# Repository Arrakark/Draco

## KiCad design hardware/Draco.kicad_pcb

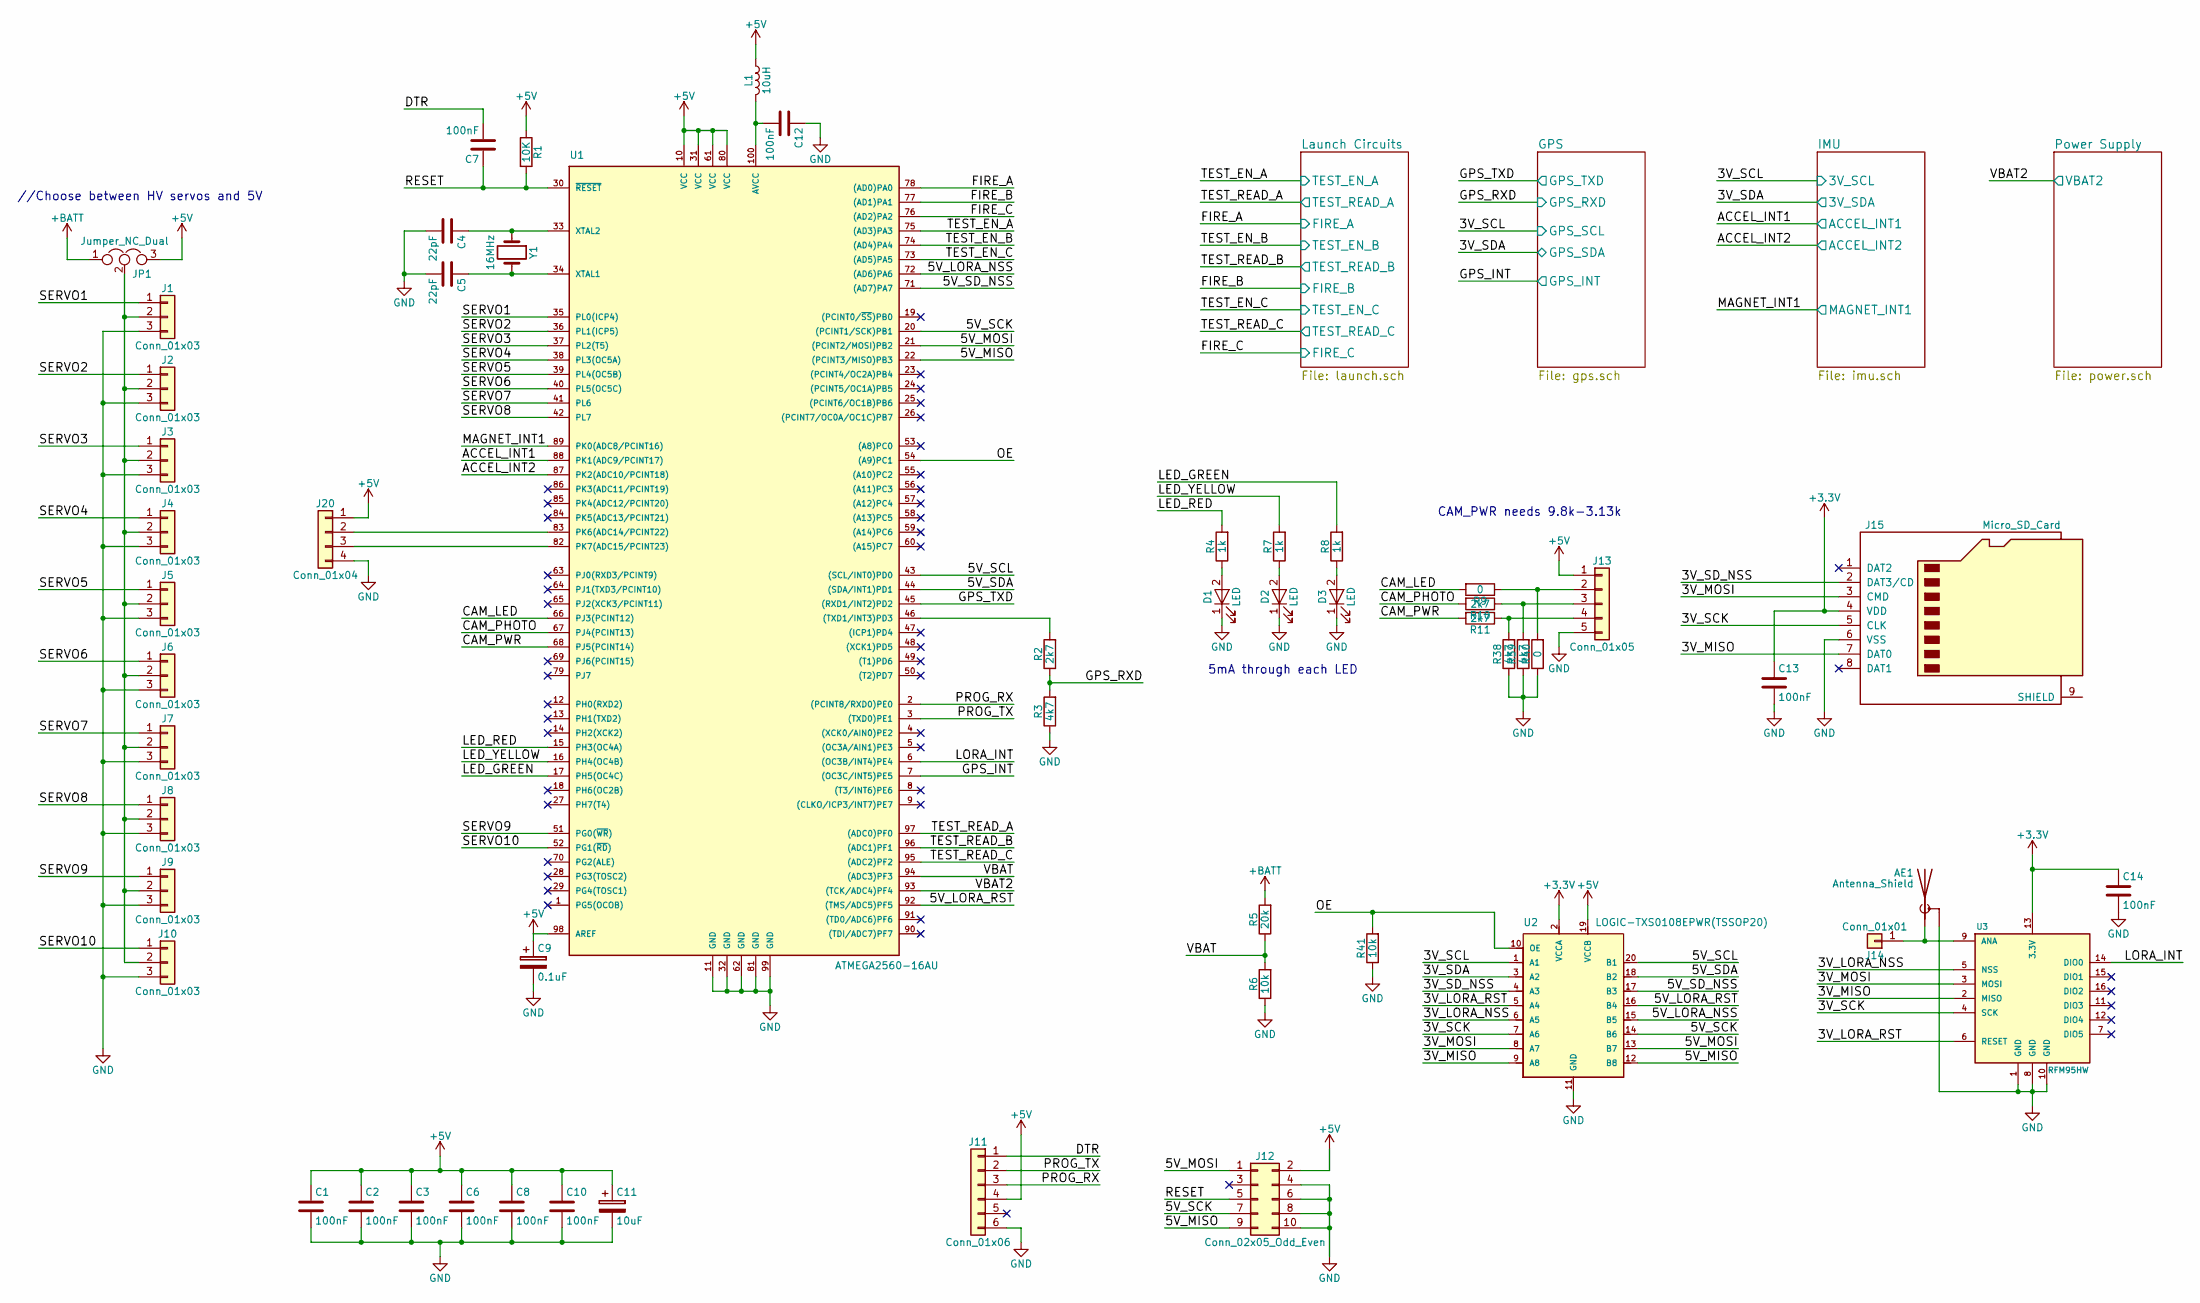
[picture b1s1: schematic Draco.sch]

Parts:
AE1: Antenna_Shield; U.FL-R-SMT
C1, C2, C3, C6, C7, C8, C10, C12, C13, C14: 100nF; C_0805
C4, C5: 22pF; C_0805
C9: 0.1uF; C_0805
C11: 10uF; C_0805
D1, D2, D3: LED; LED_0805
J1, J2, J3, J4, J5, J6, J7, J8, J9, J10: Conn_01x03; Pin_Header_Straight_1x03_Pitch2.54mm
J11: Conn_01x06; Socket_Strip_Straight_1x06_Pitch2.54mm
J12: Conn_02x05_Odd_Even; Pin_Header_Straight_2x05_Pitch2.54mm
J13: Conn_01x05; JST_XH_B05B-XH-A_05x2.50mm_Straight
J14: Conn_01x01; Pin_Header_Straight_1x01_Pitch2.54mm
J15: Micro_SD_Card; microSD_Card_Receptacle_Wuerth_693072010801
J20: Conn_01x04; JST_XH_B04B-XH-A_04x2.50mm_Straight
JP1: Jumper_NC_Dual; Pin_Header_Straight_1x03_Pitch2.54mm
L1: 10uH; L_0805
R1: 10K; R_0805
R2, R10, R11: 2k7; R_0805
R3, R38, R39: 4k7; R_0805
R4, R7, R8: 1k; R_0805
R5: 20k; R_0805
R6, R41: 10k; R_0805
R9, R40: 0; R_0805
U1: ATMEGA2560-16AU; TQFP-100_14x14mm_Pitch0.5mm
U2: LOGIC-TXS0108EPWR(TSSOP20); SSOP-20
U3: RFM95HW; Hopref_RFM9XW_SMD
Y1: 16MHz; Crystal_SMD_HC49-SD

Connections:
+5V: C1.1, C2.1, C3.1, C6.1, C8.1, C9.1, C10.1, C11.1, J11.4, J12.2, J13.1, J20.1, JP1.3, L1.1, R1.1, U1.10 (VCC), U1.31 (VCC), U1.61 (VCC), U1.80 (VCC), U1.98 (AREF), U2.19 (VCCB); also elsewhere on the board
+BATT: JP1.1, R5.2; also elsewhere on the board
/3V_LORA_NSS: U2.6 (A5), U3.5 (NSS)
/3V_LORA_RST: U2.5 (A4), U3.6 (RESET)
/3V_MISO: J15.7 (DAT0), U2.9 (A8), U3.2 (MISO)
/3V_MOSI: J15.3 (CMD), U2.8 (A7), U3.3 (MOSI)
/3V_SCK: J15.5 (CLK), U2.7 (A6), U3.4 (SCK)
/3V_SCL: U2.1 (A1); also elsewhere on the board
/3V_SDA: U2.3 (A2); also elsewhere on the board
/3V_SD_NSS: J15.2 (DAT3/CD), U2.4 (A3)
/5V_LORA_NSS: U1.72 ((AD6)PA6), U2.15 (B5)
/5V_LORA_RST: U1.92 ((TMS/ADC5)PF5), U2.16 (B4)
/5V_MISO: J12.9, U1.22 ((PCINT3/MISO)PB3), U2.12 (B8)
/5V_MOSI: J12.1, U1.21 ((PCINT2/MOSI)PB2), U2.13 (B7)
/5V_SCK: J12.7, U1.20 ((PCINT1/SCK)PB1), U2.14 (B6)
/5V_SCL: U1.43 ((SCL/INT0)PD0), U2.20 (B1)
/5V_SDA: U1.44 ((SDA/INT1)PD1), U2.18 (B2)
/5V_SD_NSS: U1.71 ((AD7)PA7), U2.17 (B3)
/ACCEL_INT1: U1.88 (PK1(ADC9/PCINT17)); also elsewhere on the board
/ACCEL_INT2: U1.87 (PK2(ADC10/PCINT18)); also elsewhere on the board
/CAM_LED: R9.2, U1.66 (PJ3(PCINT12))
/CAM_PHOTO: R10.2, U1.67 (PJ4(PCINT13))
/CAM_PWR: R11.2, U1.68 (PJ5(PCINT14))
/DTR: C7.2, J11.1
/FIRE_A: U1.78 ((AD0)PA0); also elsewhere on the board
/FIRE_B: U1.77 ((AD1)PA1); also elsewhere on the board
/FIRE_C: U1.76 ((AD2)PA2); also elsewhere on the board
/GPS_INT: U1.7 ((OC3C/INT5)PE5); also elsewhere on the board
/GPS_RXD: R2.1, R3.2; also elsewhere on the board
/GPS_TXD: U1.45 ((RXD1/INT2)PD2); also elsewhere on the board
/LED_GREEN: R8.2, U1.17 (PH5(OC4C))
/LED_RED: R4.2, U1.15 (PH3(OC4A))
/LED_YELLOW: R7.2, U1.16 (PH4(OC4B))
/LORA_INT: U1.6 ((OC3B/INT4)PE4), U3.14 (DIO0)
/MAGNET_INT1: U1.89 (PK0(ADC8/PCINT16)); also elsewhere on the board
/OE: R41.2, U1.54 ((A9)PC1), U2.10 (OE)
/PROG_RX: J11.3, U1.2 ((PCINT8/RXD0)PE0)
/PROG_TX: J11.2, U1.3 ((TXD0)PE1)
/RESET: C7.1, J12.5, R1.2, U1.30 (~RESET)
/SERVO1: J1.1, U1.35 (PL0(ICP4))
/SERVO2: J2.1, U1.36 (PL1(ICP5))
/SERVO3: J3.1, U1.37 (PL2(T5))
/SERVO4: J4.1, U1.38 (PL3(OC5A))
/SERVO5: J5.1, U1.39 (PL4(OC5B))
/SERVO6: J6.1, U1.40 (PL5(OC5C))
/SERVO7: J7.1, U1.41 (PL6)
/SERVO8: J8.1, U1.42 (PL7)
/SERVO9: J9.1, U1.51 (PG0(~WR~))
/SERVO10: J10.1, U1.52 (PG1(~RD~))
/TEST_EN_A: U1.75 ((AD3)PA3); also elsewhere on the board
/TEST_EN_B: U1.74 ((AD4)PA4); also elsewhere on the board
/TEST_EN_C: U1.73 ((AD5)PA5); also elsewhere on the board
/TEST_READ_A: U1.97 ((ADC0)PF0); also elsewhere on the board
/TEST_READ_B: U1.96 ((ADC1)PF1); also elsewhere on the board
/TEST_READ_C: U1.95 ((ADC2)PF2); also elsewhere on the board
/VBAT: R5.1, R6.2, U1.94 ((ADC3)PF3)
/VBAT2: U1.93 ((TCK/ADC4)PF4); also elsewhere on the board
GND: AE1.2 (Shield), C1.2, C2.2, C3.2, C4.2, C5.2, C6.2, C8.2, C9.2, C10.2, C11.2, C12.1, C13.2, C14.2, D1.1 (K), D2.1 (K), D3.1 (K), J1.3, J2.3, J3.3, J4.3, J5.3, J6.3, J7.3, J8.3, J9.3, J10.3, J11.6, J12.4, J12.6, J12.8, J12.10, J13.5, J15.6 (VSS), J20.4, R3.1, R6.1, R38.1, R39.1, R40.1, R41.1, U1.11 (GND), U1.32 (GND), U1.62 (GND), U1.81 (GND), U1.99 (GND), U2.11 (GND), U3.1 (GND), U3.8 (GND), U3.10 (GND); also elsewhere on the board
unnamed: AE1.1 (A), J14.1, U3.9 (ANA)
unnamed: C4.1, U1.33 (XTAL2), Y1.1
unnamed: C5.1, U1.34 (XTAL1), Y1.2
unnamed: C12.2, L1.2, U1.100 (AVCC)
unnamed: D1.2 (A), R4.1
unnamed: D2.2 (A), R7.1
unnamed: D3.2 (A), R8.1
unnamed: J1.2, J2.2, J3.2, J4.2, J5.2, J6.2, J7.2, J8.2, J9.2, J10.2, JP1.2
unnamed: J13.2, R9.1, R40.2
unnamed: J13.3, R10.1, R39.2
unnamed: J13.4, R11.1, R38.2
unnamed: J20.2, U1.83 (PK6(ADC14/PCINT22))
unnamed: J20.3, U1.82 (PK7(ADC15/PCINT23))
unnamed: R2.2, U1.46 ((TXD1/INT3)PD3)

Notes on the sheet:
//Choose between HV servos and 5V
5mA through each LED
CAM_PWR needs 9.8k-3.13k

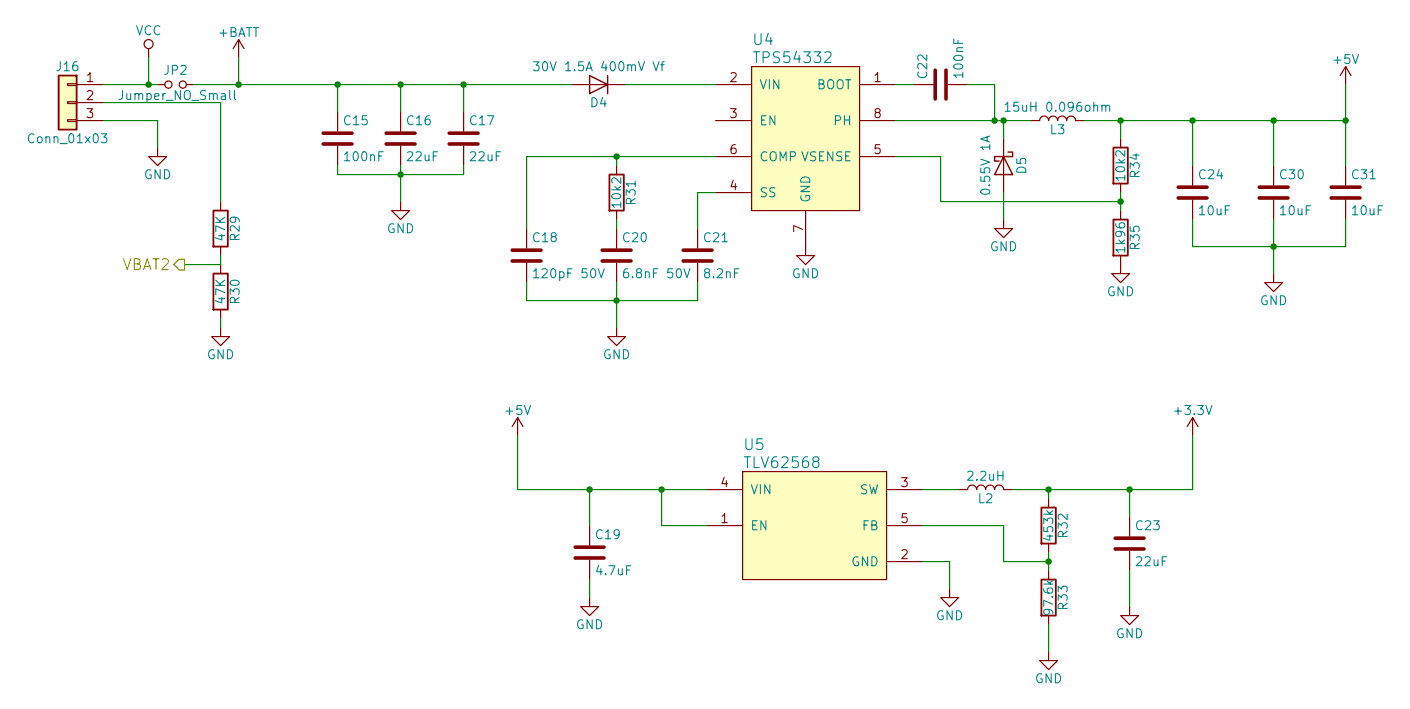
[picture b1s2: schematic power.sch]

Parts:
C15, C22: 100nF; C_0805
C16, C17, C23: 22uF; C_0805
C18: 120pF 50V; C_0805
C19: 4.7uF; C_0805
C20: 6.8nF 50V; C_0805
C21: 8.2nF; C_0805
C24, C30, C31: 10uF; C_0805
D4: 30V 1.5A 400mV Vf; D_SOD-323
D5: 0.55V 1A; D_SOD-123F
J16: Conn_01x03; JST_XH_S03B-XH-A_03x2.50mm_Angled
JP2: Jumper_NO_Small; Pin_Header_Straight_1x02_Pitch2.54mm
L2: 2.2uH; L_Taiyo-Yuden_NR-60xx
L3: 15uH 0.096ohm; L_Taiyo-Yuden_NR-60xx
R29, R30: 47K; R_0805
R31, R34: 10k2; R_0805
R32: 453k; R_0805
R33: 97.6k; R_0805
R35: 1k96; R_0805
U4: TPS54332; SOIC-8-1EP_3.9x4.9mm_Pitch1.27mm
U5: TLV62568; SOT-23-5

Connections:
+5V: C19.1, C24.1, C30.1, C31.1, L3.2, R34.1, U5.1 (EN), U5.4 (VIN); also elsewhere on the board
+BATT: C15.1, C16.1, C17.1, D4.2 (A), JP2.2; also elsewhere on the board
/VBAT2: R29.2, R30.1; also elsewhere on the board
GND: C15.2, C16.2, C17.2, C18.2, C19.2, C20.2, C21.2, C23.2, C24.2, C30.2, C31.2, D5.2 (A), J16.3, R30.2, R33.2, R35.2, U4.7 (GND), U4.9 (GND), U5.2 (GND); also elsewhere on the board
unnamed: C18.1, R31.1, U4.6 (COMP)
unnamed: C20.1, R31.2
unnamed: C21.1, U4.4 (SS)
unnamed: C22.1, U4.1 (BOOT)
unnamed: C22.2, D5.1 (K), L3.1, U4.8 (PH)
unnamed: D4.1 (K), U4.2 (VIN)
unnamed: J16.2, R29.1
unnamed: L2.1, U5.3 (SW)
unnamed: R32.2, R33.1, U5.5 (FB)
unnamed: R34.2, R35.1, U4.5 (VSENSE)
VCC: J16.1, JP2.1; also elsewhere on the board

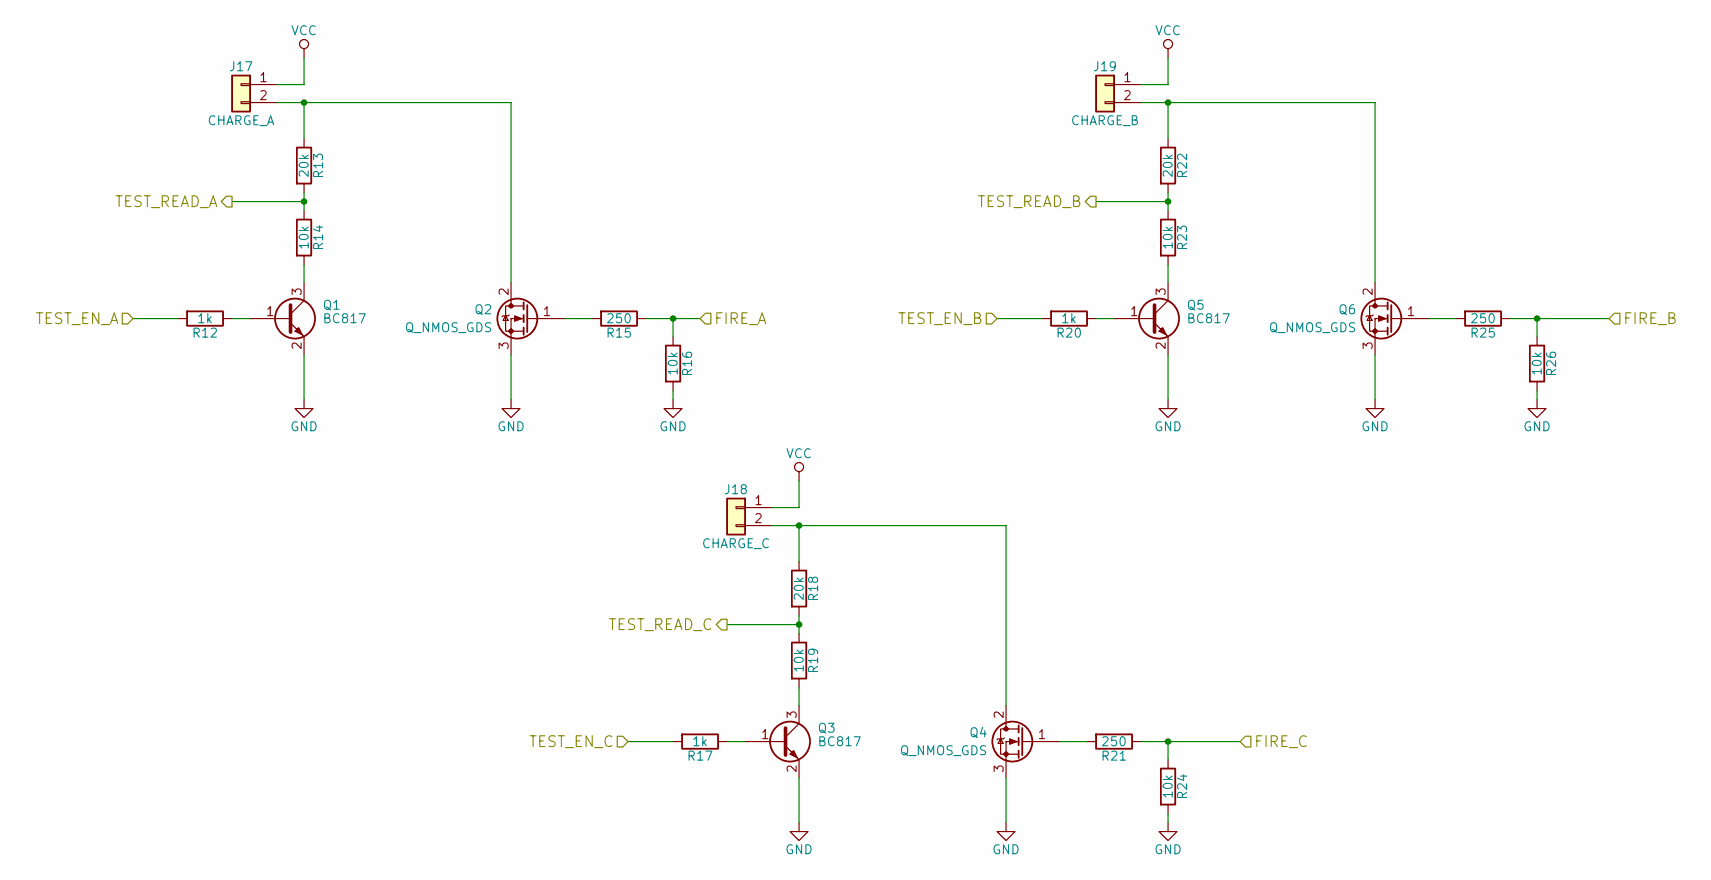
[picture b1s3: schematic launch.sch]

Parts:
J17: CHARGE_A; TerminalBlock_bornier-2_P5.08mm
J18: CHARGE_C; TerminalBlock_bornier-2_P5.08mm
J19: CHARGE_B; TerminalBlock_bornier-2_P5.08mm
Q1, Q3, Q5: BC817; SOT-23
Q2, Q4, Q6: Q_NMOS_GDS; TO-252-2
R12, R17, R20: 1k; R_0805
R13, R18, R22: 20k; R_0805
R14, R16, R19, R23, R24, R26: 10k; R_0805
R15, R21, R25: 250; R_0805

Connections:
/FIRE_A: R15.1, R16.1; also elsewhere on the board
/FIRE_B: R25.1, R26.1; also elsewhere on the board
/FIRE_C: R21.1, R24.1; also elsewhere on the board
/TEST_EN_A: R12.2; also elsewhere on the board
/TEST_EN_B: R20.2; also elsewhere on the board
/TEST_EN_C: R17.2; also elsewhere on the board
/TEST_READ_A: R13.2, R14.1; also elsewhere on the board
/TEST_READ_B: R22.2, R23.1; also elsewhere on the board
/TEST_READ_C: R18.2, R19.1; also elsewhere on the board
GND: Q1.2 (E), Q2.3 (S), Q3.2 (E), Q4.3 (S), Q5.2 (E), Q6.3 (S), R16.2, R24.2, R26.2; also elsewhere on the board
unnamed: J17.2, Q2.2 (D), R13.1
unnamed: J18.2, Q4.2 (D), R18.1
unnamed: J19.2, Q6.2 (D), R22.1
unnamed: Q1.1 (B), R12.1
unnamed: Q1.3 (C), R14.2
unnamed: Q2.1 (G), R15.2
unnamed: Q3.1 (B), R17.1
unnamed: Q3.3 (C), R19.2
unnamed: Q4.1 (G), R21.2
unnamed: Q5.1 (B), R20.1
unnamed: Q5.3 (C), R23.2
unnamed: Q6.1 (G), R25.2
VCC: J17.1, J18.1, J19.1; also elsewhere on the board

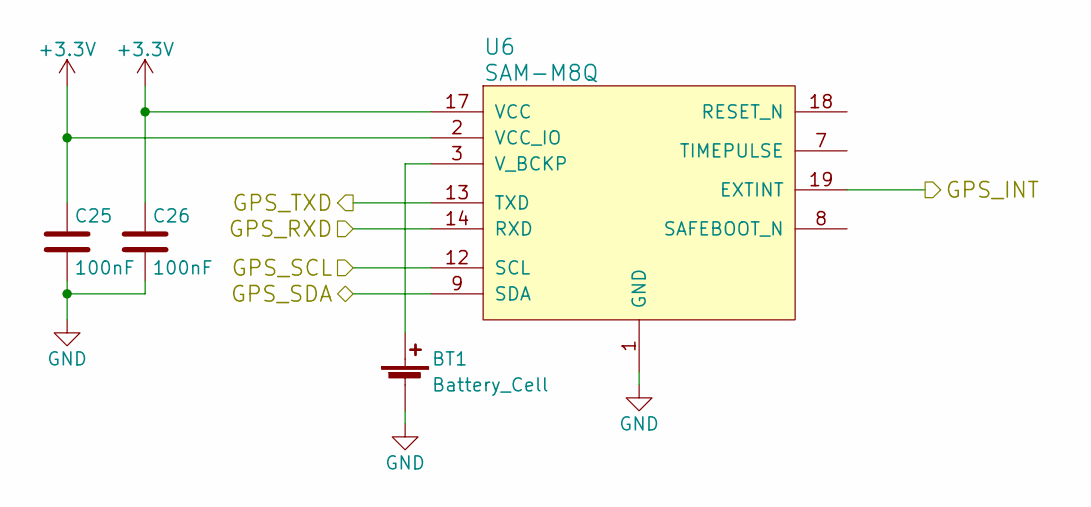
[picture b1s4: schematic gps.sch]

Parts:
BT1: Battery_Cell; Keystone_3000_1x12mm-CoinCell
C25, C26: 100nF; C_0805
U6: SAM-M8Q

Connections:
/3V_SCL: U6.12 (SCL); also elsewhere on the board
/3V_SDA: U6.9 (SDA); also elsewhere on the board
/GPS_INT: U6.19 (EXTINT); also elsewhere on the board
/GPS_RXD: U6.14 (RXD); also elsewhere on the board
/GPS_TXD: U6.13 (TXD); also elsewhere on the board
GND: BT1.2 (-), C25.2, C26.2, U6.1 (GND), U6.4 (GND), U6.5 (GND), U6.6 (GND), U6.10 (GND), U6.11 (GND), U6.15 (GND), U6.16 (GND), U6.20 (GND); also elsewhere on the board
unnamed: BT1.1 (+), U6.3 (V_BCKP)

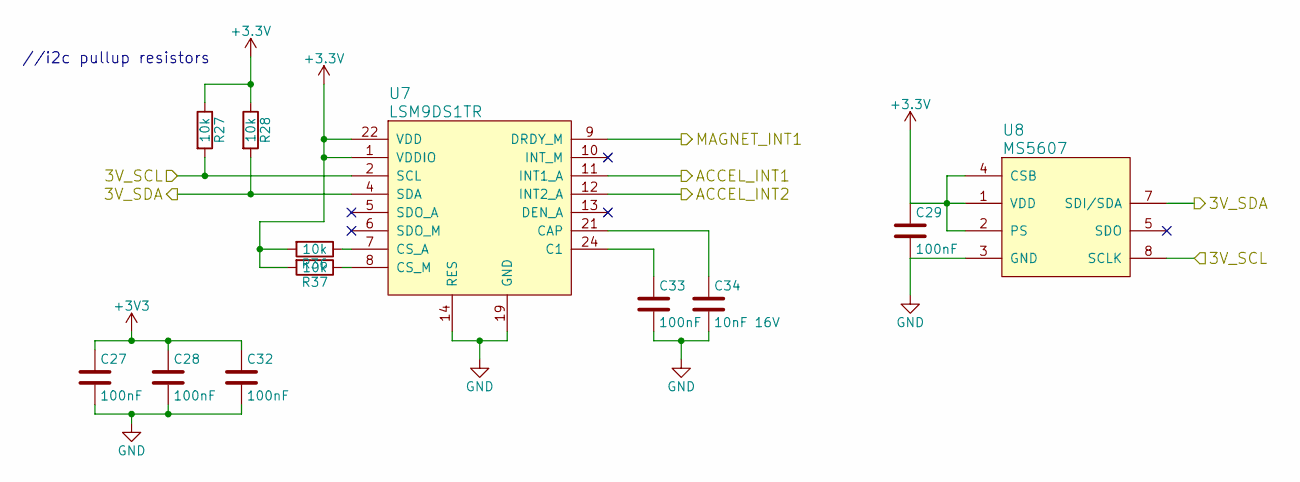
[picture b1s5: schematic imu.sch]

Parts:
C27, C28, C29, C32, C33: 100nF; C_0805
C34: 10nF 16V; C_0805
R27, R28, R36, R37: 10k; R_0805
U7: LSM9DS1TR‎; LGA-24L_3x3.5mm_Pitch0.43mm
U8: MS5607

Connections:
/3V_SCL: R27.2, U7.2 (SCL), U8.8 (SCLK); also elsewhere on the board
/3V_SDA: R28.2, U7.4 (SDA), U8.7 (SDI/SDA); also elsewhere on the board
/ACCEL_INT1: U7.11 (INT1_A); also elsewhere on the board
/ACCEL_INT2: U7.12 (INT2_A); also elsewhere on the board
/MAGNET_INT1: U7.9 (DRDY_M); also elsewhere on the board
GND: C27.2, C28.2, C29.2, C32.2, C33.2, C34.2, U7.14 (RES), U7.15 (RES), U7.16 (RES), U7.17 (RES), U7.18 (RES), U7.19 (GND), U7.20 (GND), U8.3 (GND); also elsewhere on the board
unnamed: C33.1, U7.24 (C1)
unnamed: C34.1, U7.21 (CAP)
unnamed: R36.1, U7.7 (CS_A)
unnamed: R37.1, U7.8 (CS_M)
unnamed: U8.5 (SDO), U8.6 (SDO)

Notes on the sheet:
//i2c pullup resistors

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
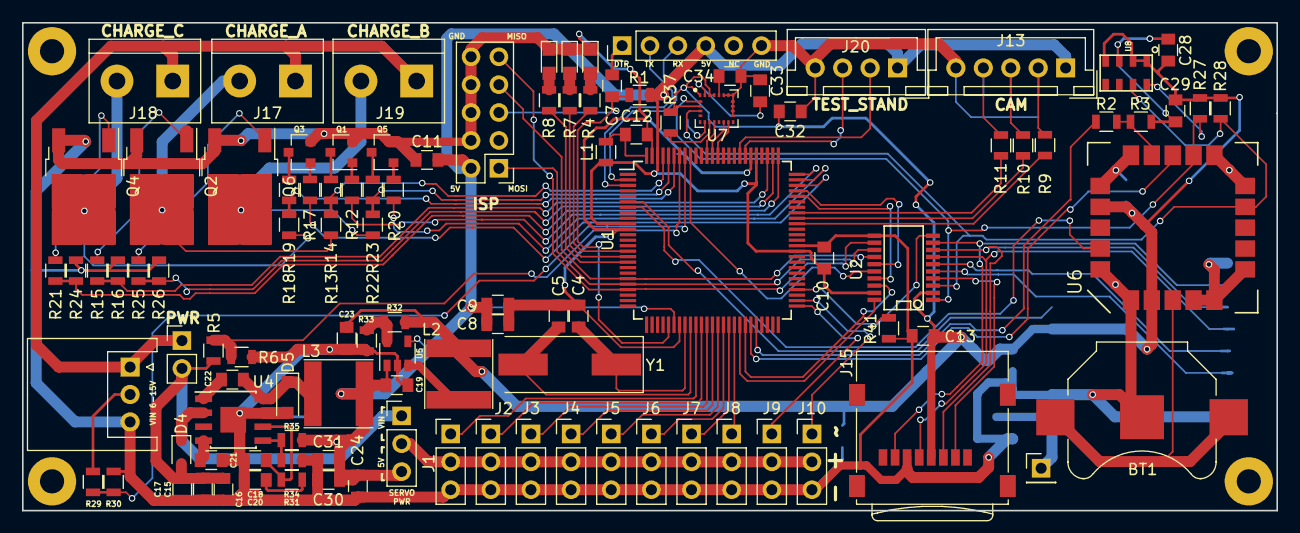
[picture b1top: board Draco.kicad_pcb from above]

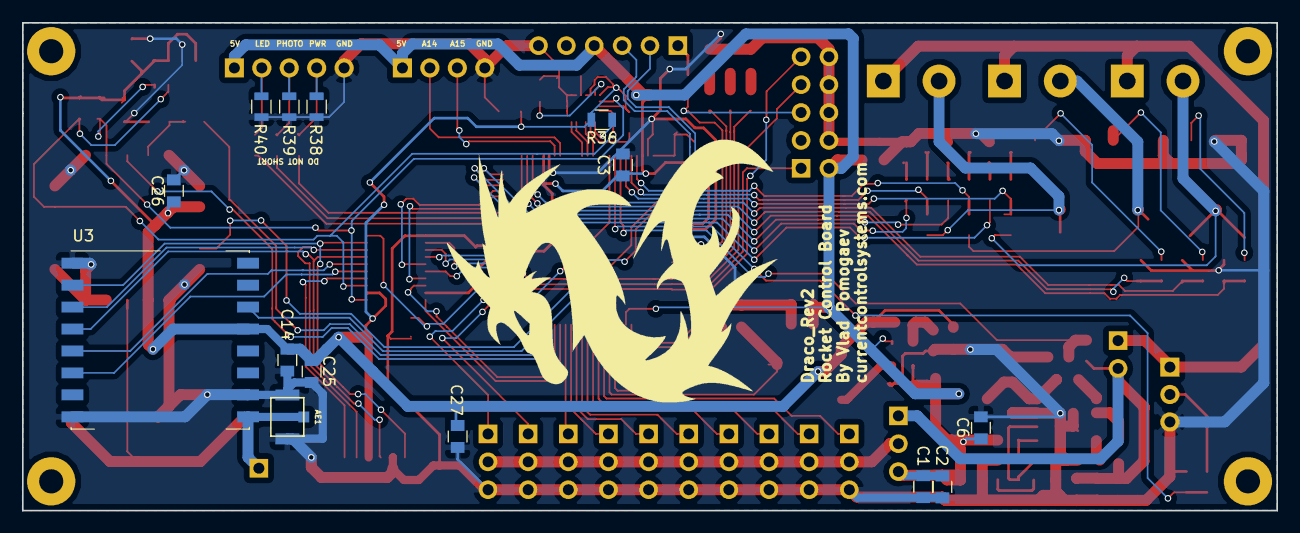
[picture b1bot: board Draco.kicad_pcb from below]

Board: 2 copper layers, 114.3 x 44.5 mm, 126 parts (14 on the bottom side), 102 nets.

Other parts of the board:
MH1, MH2, MH3, MH4: MountingHole_2.2mm_M2_Pad

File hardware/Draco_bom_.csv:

Component,Description,Part,References,Value,Footprint,Quantity Per PCB,Datasheet,Field8,Field4,Field7,Field6,Field5
1,Antenna symbol with extra pin for shielding,Antenna_Shield,AE1,Antenna_Shield,U.FL-R-SMT,1,,,,,,
2,single battery cell,Battery_Cell,BT1,Battery_Cell,Keystone_3000_1x12mm-CoinCell,1,,,,,,
3,Polarised capacitor,CP,C9,0.1uF,C_0805,1,,,,,,
4,Unpolarized capacitor,C,C1 C2 C3 C6 C7 C8 C10 C12 C13 C14 C15 C22 C25 C26 C27 C28 C29 C32 C33,100nF,C_0805,19,,,,,,
5,Unpolarized capacitor,C,C34,10nF 16V,C_0805,1,,,,,,
6,Polarised capacitor,CP,C11,10uF,C_0805,1,,,,,,
7,Unpolarized capacitor,C,C24 C30 C31,10uF,C_0805,3,,,,,,
8,Unpolarized capacitor,C,C18,120pF 50V,C_0805,1,,,,,,
9,Unpolarized capacitor,C,C4 C5,22pF,C_0805,2,,,,,,
10,Unpolarized capacitor,C,C16 C17 C23,22uF,C_0805,3,,,,,,
11,Unpolarized capacitor,C,C19,4.7uF,C_0805,1,,,,,,
12,Unpolarized capacitor,C,C20,6.8nF 50V,C_0805,1,,,,,,
13,Unpolarized capacitor,C,C21,8.2nF,C_0805,1,,,,,,
14,Schottky diode,D_Schottky,D5,0.55V 1A,D_SOD-123F,1,,,,,,
15,Diode,D,D4,30V 1.5A 400mV Vf,D_SOD-323,1,,,,,,
16,LED generic,LED,D1 D2 D3,LED,LED_0805,3,,,,,,
17,"Generic connector, single row, 01x02",Conn_01x02,J17,CHARGE_A,TerminalBlock_bornier-2_P5.08mm,1,,,,,,
18,"Generic connector, single row, 01x02",Conn_01x02,J19,CHARGE_B,TerminalBlock_bornier-2_P5.08mm,1,,,,,,
19,"Generic connector, single row, 01x02",Conn_01x02,J18,CHARGE_C,TerminalBlock_bornier-2_P5.08mm,1,,,,,,
20,"Generic connector, single row, 01x01",Conn_01x01,J14,Conn_01x01,Pin_Header_Straight_1x01_Pitch2.54mm,1,,,,,,
21,"Generic connector, single row, 01x03",Conn_01x03,J1 J2 J3 J4 J5 J6 J7 J8 J9 J10,Conn_01x03,Pin_Header_Straight_1x03_Pitch2.54mm,10,,,,,,
22,"Generic connector, single row, 01x03",Conn_01x03,J16,Conn_01x03,JST_XH_S03B-XH-A_03x2.50mm_Angled,1,,,,,,
23,"Generic connector, single row, 01x04",Conn_01x04,J20,Conn_01x04,JST_XH_B04B-XH-A_04x2.50mm_Straight,1,,,,,,
24,"Generic connector, single row, 01x05",Conn_01x05,J13,Conn_01x05,JST_XH_B05B-XH-A_05x2.50mm_Straight,1,,,,,,
25,"Generic connector, single row, 01x06",Conn_01x06,J11,Conn_01x06,Socket_Strip_Straight_1x06_Pitch2.54mm,1,,,,,,
26,"Generic connector, double row, 02x05, odd/even pin numbering scheme (row 1 odd numbers, row 2 even numbers)",Conn_02x05_Odd_Even,J12,Conn_02x05_Odd_Even,Pin_Header_Straight_2x05_Pitch2.54mm,1,,,,,,
27,Micro SD Card Socket,Micro_SD_Card,J15,Micro_SD_Card,microSD_Card_Receptacle_Wuerth_693072010801,1,http://katalog.we-online.de/em/datasheet/693072010801.pdf,,,,,
28,"Dual Jumper, normally closed",Jumper_NC_Dual,JP1,Jumper_NC_Dual,Pin_Header_Straight_1x03_Pitch2.54mm,1,,,,,,
29,"Jumper, normally open",Jumper_NO_Small,JP2,Jumper_NO_Small,Pin_Header_Straight_1x02_Pitch2.54mm,1,,,,,,
30,Inductor,L,L1,10uH,L_0805,1,,,,,,
31,Inductor,L,L3,15uH 0.096ohm,L_Taiyo-Yuden_NR-60xx,1,,,,,,
32,Inductor,L,L2,2.2uH,L_Taiyo-Yuden_NR-60xx,1,,,,,,
33,"45V Vce, 0.8A Ic, NPN, SOT-23",BC817,Q1 Q3 Q5,BC817,SOT-23,3,http://www.fairchildsemi.com/ds/BC/BC817.pdf,,,,,
34,Transistor N-MOSFET (general),Q_NMOS_DGS,Q2 Q4 Q6,Q_NMOS_DGS,TO-252-2,3,,,,,,
35,Resistor,R,R9 R40,0,R_0805,2,,,,,,
36,Resistor,R,R1 R6 R14 R16 R19 R23 R24 R26 R27 R28 R36 R37 R41,10K,R_0805,13,,,,,,
37,Resistor,R,R31 R34,10k2,R_0805,2,,,,,,
38,Resistor,R,R4 R7 R8 R12 R17 R20,1k,R_0805,6,,,,,,
39,Resistor,R,R35,1k96,R_0805,1,,,,,,
40,Resistor,R,R5 R13 R18 R22,20k,R_0805,4,,,,,,
41,Resistor,R,R15 R21 R25,250,R_0805,3,,,,,,
42,Resistor,R,R2 R10 R11,2k7,R_0805,3,,,,,,
43,Resistor,R,R32,453k,R_0805,1,,,,,,
44,Resistor,R,R29 R30,47K,R_0805,2,,,,,,
45,Resistor,R,R3 R38 R39,4k7,R_0805,3,,,,,,
46,Resistor,R,R33,97.6k,R_0805,1,,,,,,
47,"TQFP100, 128k Flash, 8k SRAM, 4k EEPROM, JTAG",ATMEGA2560-16AU,U1,ATMEGA2560-16AU,TQFP-100_14x14mm_Pitch0.5mm,1,http://www.atmel.com/Images/Atmel-2549-8-bit-AVR-Microcontro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,,,,,
48,,LOGIC-TXS0108EPWR(TSSOP20),U2,LOGIC-TXS0108EPWR(TSSOP20),SSOP-20,1,Texas Instruments,IC 8BIT NON-INV TRANSLTR 20TSSOP,TSSOP-20 Texas Instruments,TXS0108EPWR,Good,1.26 USD
49,,LSM9DS1TR‎,U7,LSM9DS1TR‎,LGA-24L_3x3.5mm_Pitch0.43mm,1,,,,,,
50,,MS5607,U8,MS5607,MS5607,1,,,,,,
51,"RFM95HW, LORA +20dBm HopeRF Wireless Transceiver, Vcc=3.3V",RFM95HW,U3,RFM95HW,Hopref_RFM9XW_SMD,1,https://cdn-learn.adafruit.com/assets/assets/000/031/659/ori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,,,,,
52,,SAM-M8Q,U6,SAM-M8Q,SAM-M8Q,1,,,,,,
53,,TLV62568,U5,TLV62568,SOT-23-5,1,,,,,,
54,,TPS54332,U4,TPS54332,SOIC-8-1EP_3.9x4.9mm_Pitch1.27mm,1,,,,,,
55,Two pin crystal,Crystal,Y1,16MHz,Crystal_SMD_HC49-SD,1,,,,,,
,,,,,,,,,,,,
,,,,,,,,,,,,
,,,,,,,,,,,,
,,,,,,,,,,,,
,,,,,,,,,,,,
Component Groups:,55,,,,,,,,,,,
Component Count:,122,,,,,,,,,,,
Fitted Components:,122,,,,,,,,,,,
Number of PCBs:,1,,,,,,,,,,,
Total components:,122,,,,,,,,,,,
Schematic Version:,,,,,,,,,,,,
Schematic Date:,,,,,,,,,,,,
BoM Date:,1/31/2018 10:25:15 AM,,,,,,,,,,,
Schematic Source:,C:/Users/vlad/Documents/Personal Projects/Draco/Draco.sch,,,,,,,,,,,
KiCad Version:,Eeschema 4.0.7,,,,,,,,,,,

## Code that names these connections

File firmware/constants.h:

#ifndef MY_DEFINES_H
#define MY_DEFINES_H

#define FIRE_A 22
#define FIRE_B 23
#define FIRE_C 24
#define TEST_EN_A 25
#define TEST_EN_B 26
#define TEST_EN_C 27

#define LORA_NSS 28
#define SD_NSS 29

#define LVL_EN 36

#define SERVO1 49
#define SERVO2 48
#define SERVO3 47
#define SERVO4 46
#define SERVO5 45
#define SERVO6 44
#define SERVO7 43
#define SERVO8 42
#define SERVO9 41
#define SERVI10 40


#define MAGNET_INT 62
#define ACCEL_INT1 63
#define ACCEL_INT2 64

//DDRJ = DDRJ | B00110000;
//PORTJ = B10101000; // sets digital pins 7,5,3 HIGH
//camera not in Arduino ide; must use port manipulation to read and write camera values. Write functions for these plz.
//CAM_LED PJ3 
//CAM_PHOTO PJ4 
//CAM_PWR PJ5 

#define LED_RED 6
#define LED_YELLOW 7
#define LED_GREEN 8

#define LORA_RST 59
#define VBAT_1S 58
#define VBAT_2S 57
#define TEST_READ_C 56
#define TEST_READ_B 55
#define TEST_READ_A 54

#define LORA_INT 2
#define GPS_INT 3

//GPS is connected to Serial1 not Serial

#define TEST_STAND_DOUT 68
#define TEST_STAND_SCK 69

#endif

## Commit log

2018-01-17 replaced the level-shifter
2018-01-18 added sd card
2018-01-21 Did design review. Changed/confirmed voltage levels
2018-01-22 Started Board layout
2018-01-22 Finished charge layout
2018-01-23 Started board placement
2018-01-23 Routed crystal; might not be permenant spot
2018-01-23 Added parts list to power budget
2018-01-25 recalculated power and added new supply schem.
2018-01-25 pushed new psu to pcb
2018-01-25 Doing PCB Layout
2018-01-25 moved charge module, routed lots of stuff
2018-01-25 moving blocks around
2018-01-26 Routed 50%
2018-01-26 Routed 60%
2018-01-26 Backtracked to 30%
2018-01-27 Finished left side
2018-01-28 80% done routing
2018-01-28 Adding bypass capacitors
2018-01-28 Added logo files and BOM
2018-01-28 Finished preliminary layout
2018-01-29 Halfway Done Labeling
2018-01-29 Done reogrinizing labels
2018-01-29 Added dragon
2018-01-29 Starting design review
2018-01-29 Added camera resistor divider
2018-01-30 work review
2018-01-30 Added camera power
2018-01-30 Added logo again because the dragon keeps dissapearing
2018-01-30 Figured out where the dragon goes
2018-01-30 Added website
2018-01-30 Added GERBERS
2018-01-30 Added IDC library
2018-01-31 Fixed MOSFET pinout
2018-01-31 Fixed MOSFET ground plane
2018-01-31 Finished
2018-02-10 Fixed unconnected pins and finished pin_define.txt
2018-02-25 moved hardware to hardware folder
2018-02-25 Added new folders
2018-02-25 Uploaded some other files
2018-02-25 Added barometer base library
2018-02-25 Changed settings
2018-02-26 added settings
2018-03-05 added scale calibration
2018-03-10 Adding libraries
2018-03-12 Added constants.h and logger class
2018-03-12 update to ide
2018-03-12 moved onto platformio
2018-03-12 testing platformio
2018-03-15 added timer
2018-03-15 Added timed events
2018-03-15 Fixed events
2018-03-15 Finished rev 1 of test_stand code
2018-03-15 updated main
2018-03-15 Added igniter testing subroutine
2018-03-22 Added simulation data
